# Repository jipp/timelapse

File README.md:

# timelapse
ATtiny 2313 based timelapse controller.

## The following features are implemented
* 10 programs to select different time intervals
* 7-segment LED will be disabled after some time and reenabled after pressing button showing the lastest selected program
* selected program will be stored in EEPROM

## Installation
Put the timelapse folder into the local Arduino folder.

## Additional files
EAGLE files included:
* Circuit diagram
* Board layout

## Info
This was developed 1st for a Nikon, but as a 2.5mm Jack is used to connect the camera any camera adapter should work.

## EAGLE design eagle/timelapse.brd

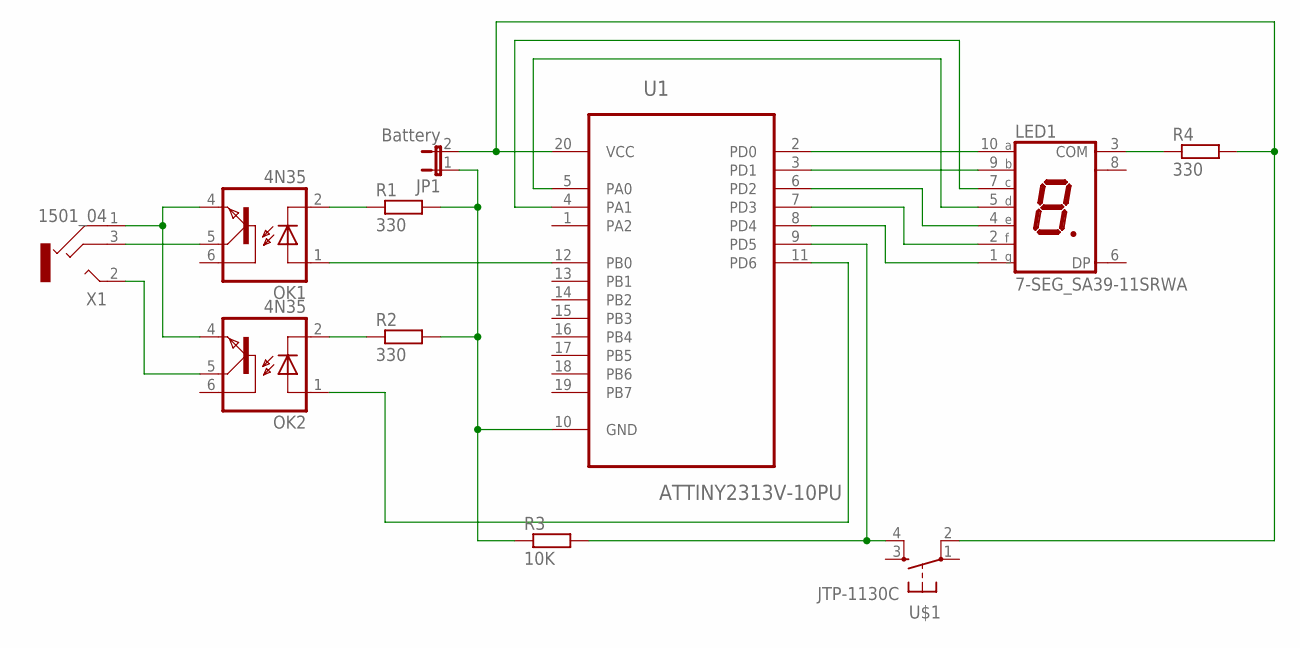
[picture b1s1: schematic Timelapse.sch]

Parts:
JP1: Battery; JP1
LED1: 7-SEG_SA39-11SRWA; SA39-11SRWA
OK1, OK2: 4N35; DIL06
R1, R2, R4: 330; 0204/7
R3: 10K; 0204/7
U1: ATTINY2313V-10PU; DIP254P762X533-20
U$1: JTP-1130C; JTP-1130
X1: 1501_04; 1501_05

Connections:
unnamed: LED1.10 (A), U1.2 (PD0)
unnamed: LED1.9 (B), U1.3 (PD1)
unnamed: LED1.4 (E), U1.6 (PD2)
unnamed: LED1.2 (F), U1.7 (PD3)
unnamed: LED1.1 (G), U1.8 (PD4)
unnamed: LED1.7 (C), U1.4 (PA1)
unnamed: LED1.5 (D), U1.5 (PA0)
unnamed: LED1.3 (COM), R4.1
unnamed: JP1.2, R4.2, U1.20 (VCC), U$1.2 (P1)
unnamed: R3.2, U1.9 (PD5), U$1.4 (S1)
unnamed: JP1.1, R1.2, R2.2, R3.1, U1.10 (GND)
unnamed: OK2.1 (A), U1.11 (PD6)
unnamed: OK2.2 (C), R2.1
unnamed: OK1.2 (C), R1.1
unnamed: OK1.1 (A), U1.12 (PB0)
unnamed: OK1.4 (EMI), OK2.4 (EMI), X1.1
unnamed: OK1.5 (COL), X1.3
unnamed: OK2.5 (COL), X1.2

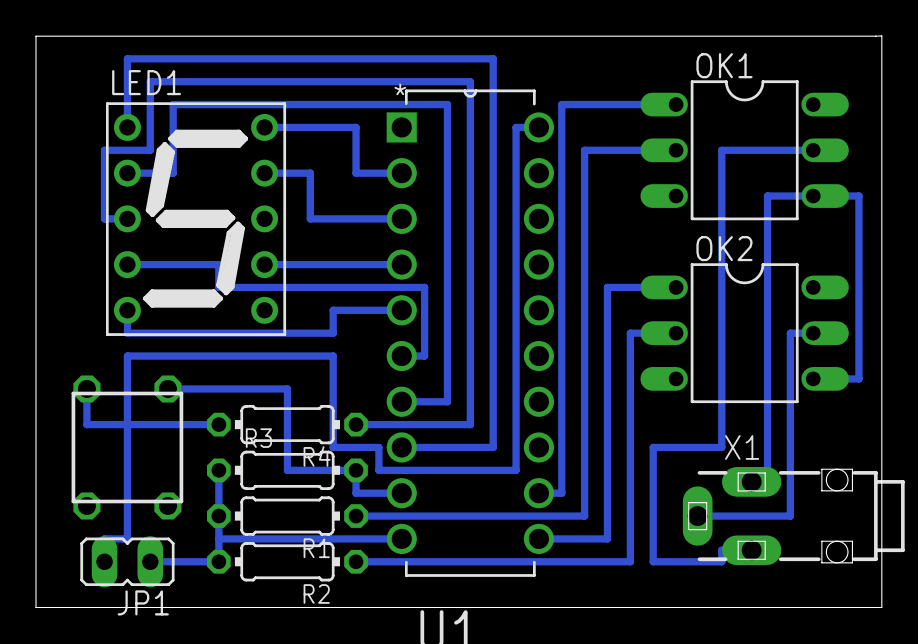
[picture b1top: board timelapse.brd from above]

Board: 2 copper layers, 47.0 x 31.8 mm, 11 parts (0 on the bottom side), 18 nets.

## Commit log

2015-04-12 init file
2015-04-12 introduce pin for shutter and focus
2015-04-12 added focus and shutter mechanism
2015-04-12 1st memory optimisation
2015-04-13 Update timelapse.ino
    Memory optimization
2015-04-16 bug fixes button and "3" not correct
2015-04-16 fixed the "3" again
2015-04-19 add EAGLE files
2015-04-20 updated README.md with general info
2015-04-20 changed 3mm -> 2.5mm
2015-04-20 updated eagle with small changes
    -move jumper
    -rearrange diagram
2015-04-21 ignore eagle.epf
2015-04-21 change of board layout - smaller
2015-04-21 rename of files
2015-04-24 ASLR -> DSLR
2015-05-01 remove include for Arduino.h
2017-11-12 added license
